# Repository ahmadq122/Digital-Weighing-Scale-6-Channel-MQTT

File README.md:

# Digital-Weighing-Scale-Board-6-Channels-MQTT
The board uses ESP32 Dev Board as the microcontroller with Nextion 3.2" Enhanced LCD Touch as a User Interface, made in portable form, and easy to use. Real Time Operating System (FreeRTOS) was applied to get better code structure and device performance. Weighing can be performed on 6 different objects at the same time, with adjustable maximum weighing on each channel. Use 3 pcs of IC ADS1232 as an Analog to Digital Converter. Calibration sensor feature available, with a maximum of 8 calibration points. 3 data logging types are available, which are Local via Micro SD card, Serial UART, and logging through MQTT Protocol.

The code programming is done in IDE: Visual Studio Code - Platform IO, Framework: Arduino

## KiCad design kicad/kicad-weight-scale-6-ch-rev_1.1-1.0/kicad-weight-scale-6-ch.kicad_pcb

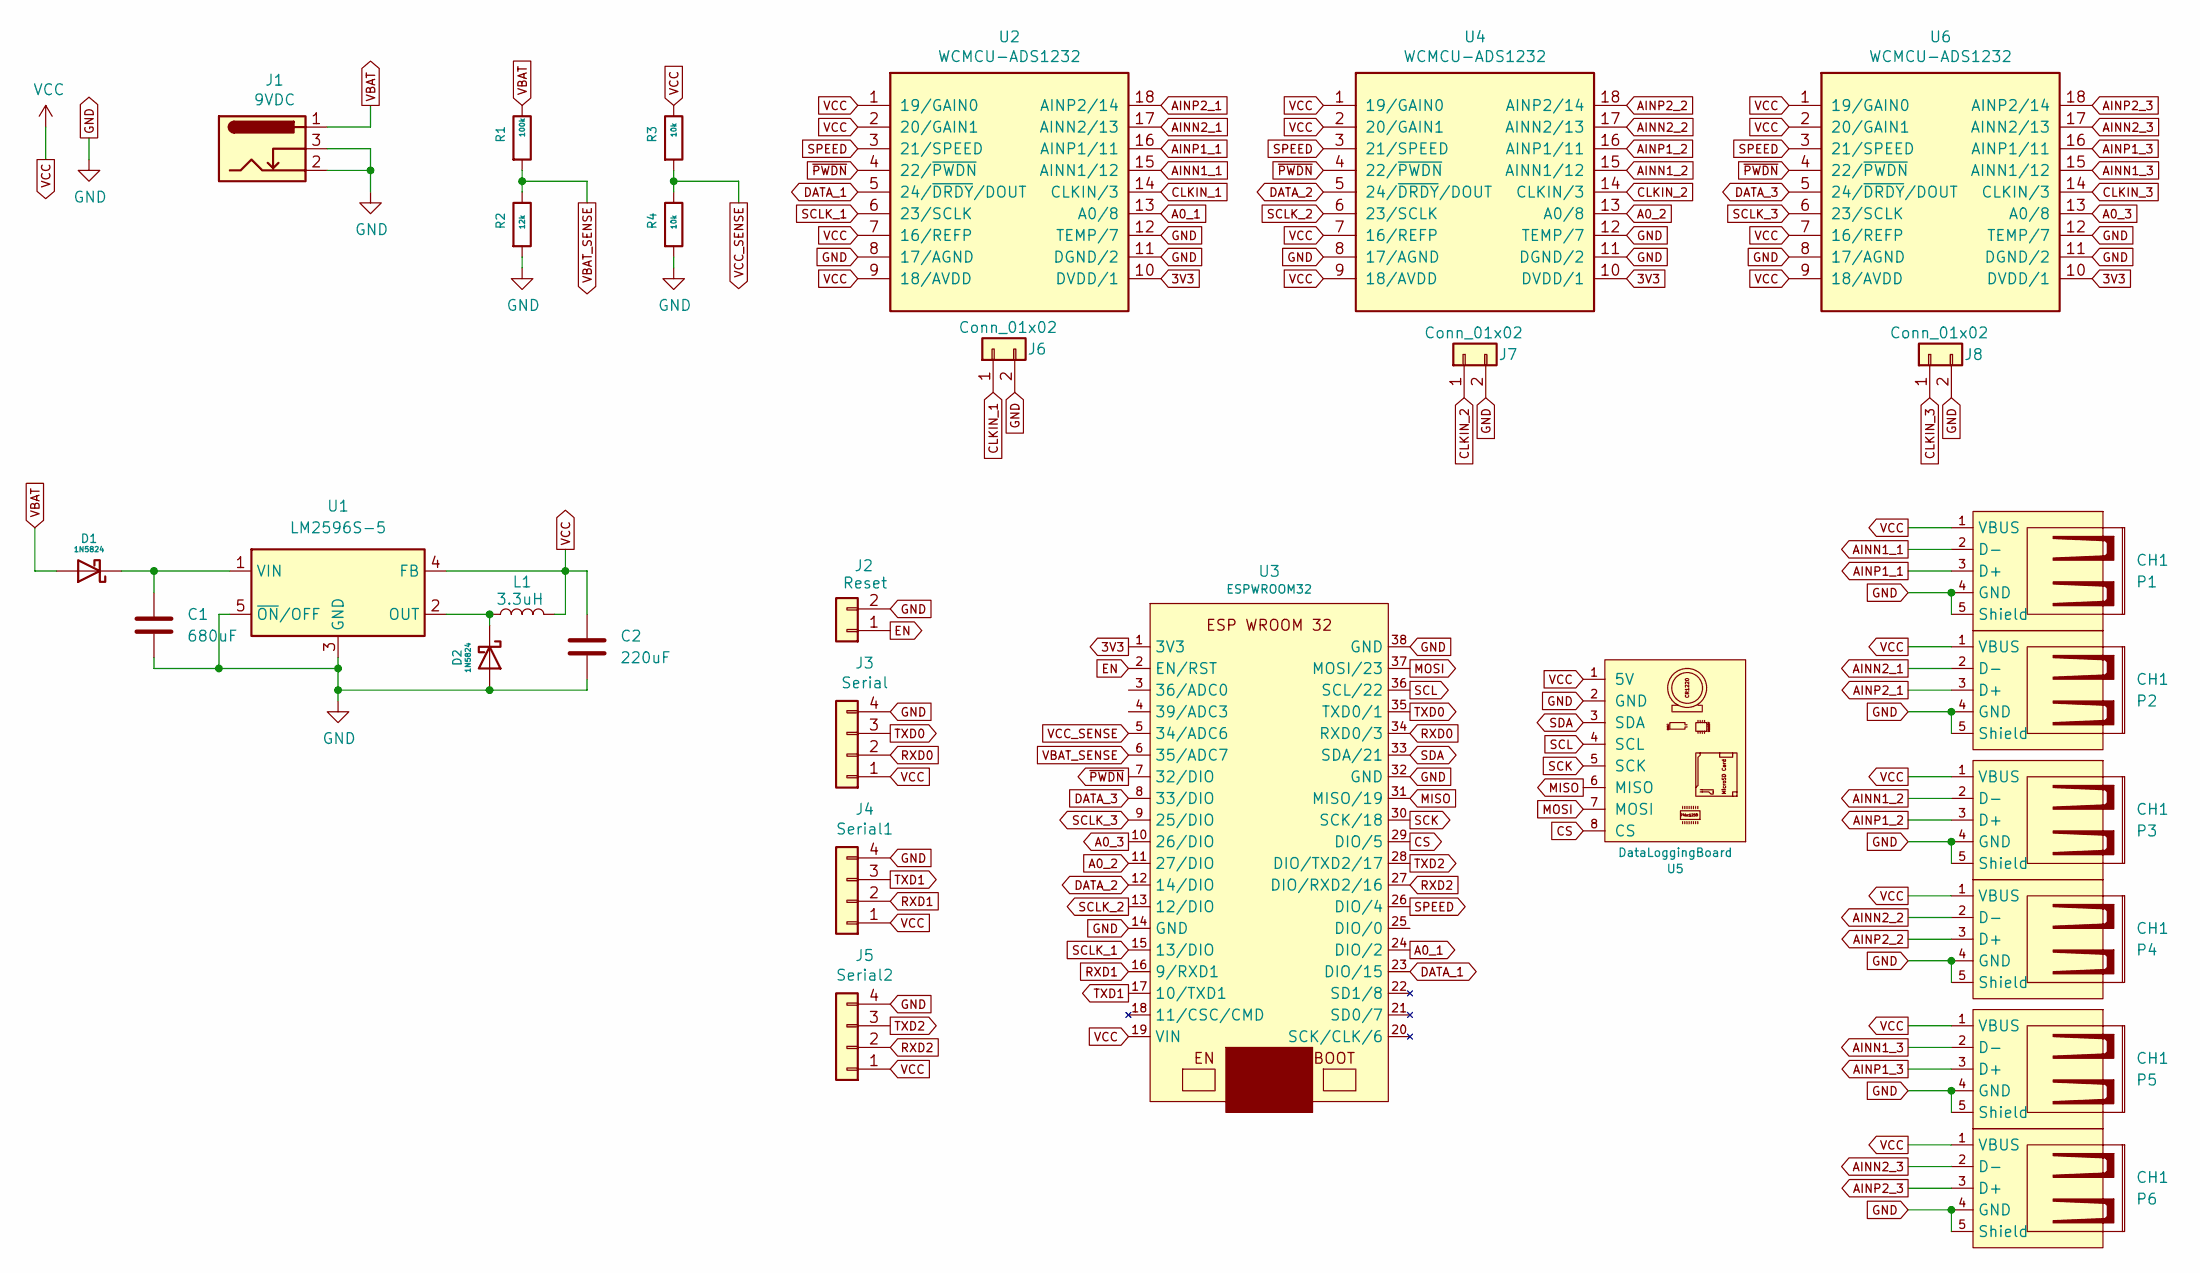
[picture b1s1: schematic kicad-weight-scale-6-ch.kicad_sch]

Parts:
C1: 680uF; CP_Elec_6.3x9.9
C2: 220uF; CP_Elec_6.3x9.9
D1, D2: 1N5824; D_SMA
J1: 9VDC; BarrelJack_Horizontal
J2: Reset; PinHeader_1x02_P2.54mm_Vertical
J3: Serial; JST_XH_B4B-XH-A_1x04_P2.50mm_Vertical
J4: Serial1; JST_XH_B4B-XH-A_1x04_P2.50mm_Vertical
J5: Serial2; JST_XH_B4B-XH-A_1x04_P2.50mm_Vertical
J6, J7, J8: Conn_01x02; PinHeader_1x02_P2.54mm_Vertical
L1: 3.3uH; L_12x12mm_H4.5mm
P1, P2, P3, P4, P5, P6: CH1; USB_A_CONNFLY_DS1095-WNR0
R1: 100k; R_0805_2012Metric_Pad1.20x1.40mm_HandSolder
R2: 12k; R_0805_2012Metric_Pad1.20x1.40mm_HandSolder
R3, R4: 10k; R_0805_2012Metric_Pad1.20x1.40mm_HandSolder
U1: LM2596S-5; TO-263-5_TabPin3
U2, U4, U6: WCMCU-ADS1232; wcmcu-ads1232
U3: ESPWROOM32; esp wroom 32 board
U5: DataLoggingBoard; Datalogging board

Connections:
3V3: U2.10 (DVDD/1), U3.1 (3V3), U4.10 (DVDD/1), U6.10 (DVDD/1)
A0_1: U2.13 (A0/8), U3.24 (DIO/2)
A0_2: U3.11 (27/DIO), U4.13 (A0/8)
A0_3: U3.10 (26/DIO), U6.13 (A0/8)
AINN1_1: P1.2 (D-), U2.15 (AINN1/12)
AINN1_2: P3.2 (D-), U4.15 (AINN1/12)
AINN1_3: P5.2 (D-), U6.15 (AINN1/12)
AINN2_1: P2.2 (D-), U2.17 (AINN2/13)
AINN2_2: P4.2 (D-), U4.17 (AINN2/13)
AINN2_3: P6.2 (D-), U6.17 (AINN2/13)
AINP1_1: P1.3 (D+), U2.16 (AINP1/11)
AINP1_2: P3.3 (D+), U4.16 (AINP1/11)
AINP1_3: P5.3 (D+), U6.16 (AINP1/11)
AINP2_1: P2.3 (D+), U2.18 (AINP2/14)
AINP2_2: P4.3 (D+), U4.18 (AINP2/14)
AINP2_3: P6.3 (D+), U6.18 (AINP2/14)
CLKIN_1: J6.1, U2.14 (CLKIN/3)
CLKIN_2: J7.1, U4.14 (CLKIN/3)
CLKIN_3: J8.1, U6.14 (CLKIN/3)
CS: U3.29 (DIO/5), U5.8 (CS)
DATA_1: U2.5 (24/~DRDY/DOUT), U3.23 (DIO/15)
DATA_2: U3.12 (14/DIO), U4.5 (24/~DRDY/DOUT)
DATA_3: U3.8 (33/DIO), U6.5 (24/~DRDY/DOUT)
EN: J2.1, U3.2 (EN/RST)
GND: C1.2, C2.2, D2.2 (A), J1.2, J1.3, J2.2, J3.4, J4.4, J5.4, J6.2, J7.2, J8.2, P1.4 (GND), P1.5 (Shield), P2.4 (GND), P2.5 (Shield), P3.4 (GND), P3.5 (Shield), P4.4 (GND), P4.5 (Shield), P5.4 (GND), P5.5 (Shield), P6.4 (GND), P6.5 (Shield), R2.2, R4.2, U1.3 (GND), U1.5 (~ON/OFF), U2.8 (17/AGND), U2.11 (DGND/2), U2.12 (TEMP/7), U3.14 (GND), U3.32 (GND), U3.38 (GND), U4.8 (17/AGND), U4.11 (DGND/2), U4.12 (TEMP/7), U5.2 (GND), U6.8 (17/AGND), U6.11 (DGND/2), U6.12 (TEMP/7)
MISO: U3.31 (MISO/19), U5.6 (MISO)
MOSI: U3.37 (MOSI/23), U5.7 (MOSI)
unnamed: C1.1, D1.1 (K), U1.1 (VIN)
unnamed: D2.1 (K), L1.1, U1.2 (OUT)
RXD0: J3.2, U3.34 (RXD0/3)
RXD1: J4.2, U3.16 (9/RXD1)
RXD2: J5.2, U3.27 (DIO/RXD2/16)
SCK: U3.30 (SCK/18), U5.5 (SCK)
SCL: U3.36 (SCL/22), U5.4 (SCL)
SCLK_1: U2.6 (23/SCLK), U3.15 (13/DIO)
SCLK_2: U3.13 (12/DIO), U4.6 (23/SCLK)
SCLK_3: U3.9 (25/DIO), U6.6 (23/SCLK)
SDA: U3.33 (SDA/21), U5.3 (SDA)
SPEED: U2.3 (21/SPEED), U3.26 (DIO/4), U4.3 (21/SPEED), U6.3 (21/SPEED)
TXD0: J3.3, U3.35 (TXD0/1)
TXD1: J4.3, U3.17 (10/TXD1)
TXD2: J5.3, U3.28 (DIO/TXD2/17)
VBAT: D1.2 (A), J1.1, R1.1
VBAT_SENSE: R1.2, R2.1, U3.6 (35/ADC7)
VCC: C2.1, J3.1, J4.1, J5.1, L1.2, P1.1 (VBUS), P2.1 (VBUS), P3.1 (VBUS), P4.1 (VBUS), P5.1 (VBUS), P6.1 (VBUS), R3.1, U1.4 (FB), U2.1 (19/GAIN0), U2.2 (20/GAIN1), U2.7 (16/REFP), U2.9 (18/AVDD), U3.19 (VIN), U4.1 (19/GAIN0), U4.2 (20/GAIN1), U4.7 (16/REFP), U4.9 (18/AVDD), U5.1 (5V), U6.1 (19/GAIN0), U6.2 (20/GAIN1), U6.7 (16/REFP), U6.9 (18/AVDD)
VCC_SENSE: R3.2, R4.1, U3.5 (34/ADC6)
~PWDN: U2.4 (22/~PWDN), U3.7 (32/DIO), U4.4 (22/~PWDN), U6.4 (22/~PWDN)

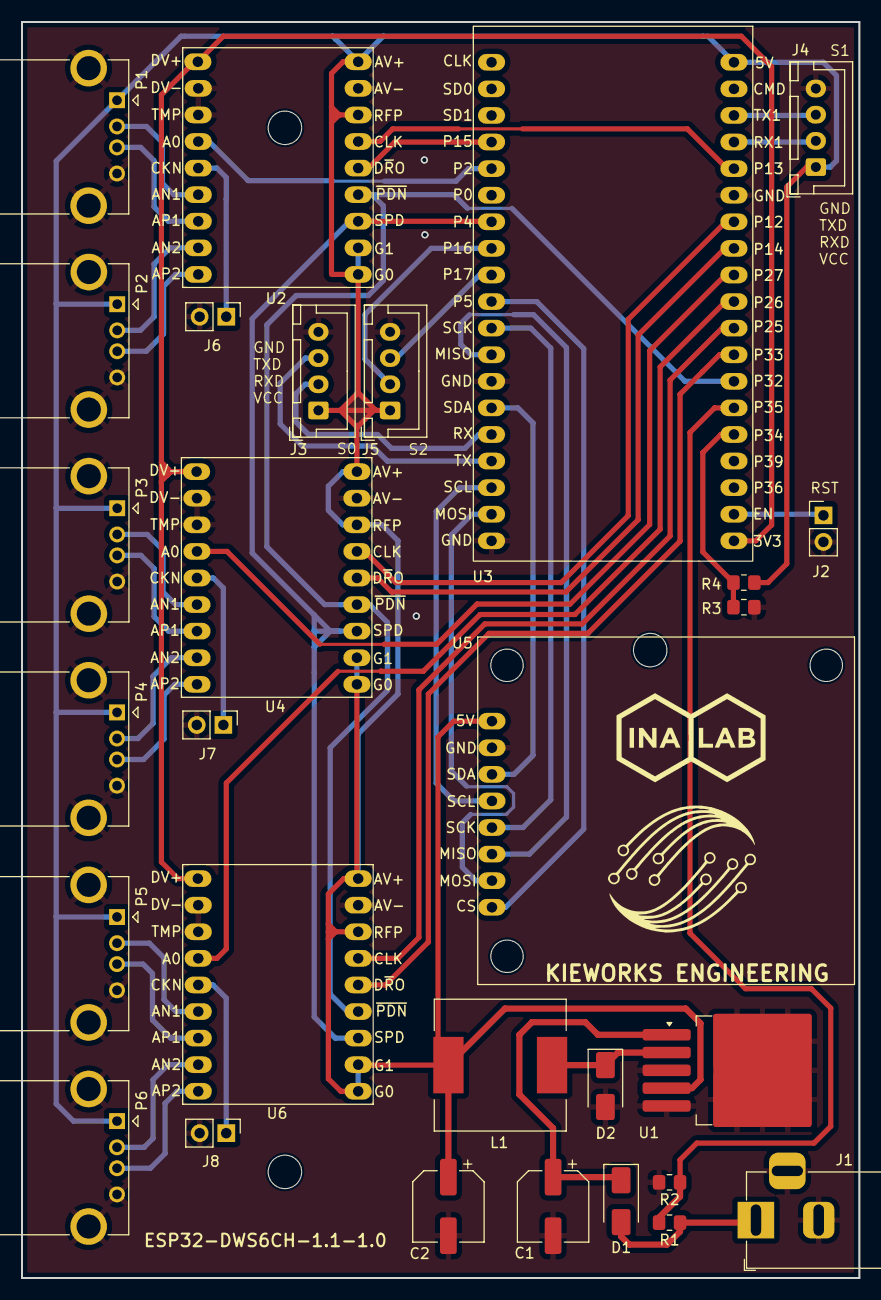
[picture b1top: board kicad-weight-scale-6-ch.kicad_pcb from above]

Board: 2 copper layers, 80.0 x 120.0 mm, 29 parts (0 on the bottom side), 47 nets.

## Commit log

2024-05-29 Remove vcc contrl & buzzer, update stack size, 2 type off req
2024-05-30 Setup MQTT publisher
2024-05-30 Updateg remote data log screen
2024-06-11 , String to char*, Receive server setup from display
2024-07-01 Update PCB file and place an order to JLCPCB
2024-07-02 Add option to use 8MB flash memory
